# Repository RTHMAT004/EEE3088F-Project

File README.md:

# EEE3088F-Project
Power and Sensing repository for the EEE3088F Project. Group 24: RTHMAT004 and CLRMAT005

This repository contains files for both the sensing and power subsystems of a Micromouse for a university project. This project involved developing a Micromouse, therefore these solutions are built with existing systems in mind (microcontroller, servo motors etc). 

The power system deals with powering the two motors of the Micromouse, managing the charging of the battery and turning the Micromouse on and off.

The sensing system deals with surface detection around the Micromouse, inevitabely helping the micromouse navigate. The sensor does not make decisions of movement, or deal with any power control, it's only purpose is to detect objects and returning results using a voltage output signal. 

# Sensing subsystem:
The folder named "SensorKiCad-RTHMAT004" contains the KiCad files for the sensor subsystem. This subsystem solves the problem of sensing for the micromouse. This subsystem uses IR frequencies to detect objects within the bounds of the sensor. This subsystem solution should be used as a springboard for ideas surrounding sensing for devices such as a micromouse.  

# Power Subsytem
The folder named "PowerKiCad-CLRMAT005" contains the KiCad files for the power subsystem. This subsystem manages everything involving the powering of the Micromouse. This subsystem uses integrated circuits to control the motors and charging of the mouse. This subsystem solution should be used as a springboard for ideas surrounding the powering of small robotics.

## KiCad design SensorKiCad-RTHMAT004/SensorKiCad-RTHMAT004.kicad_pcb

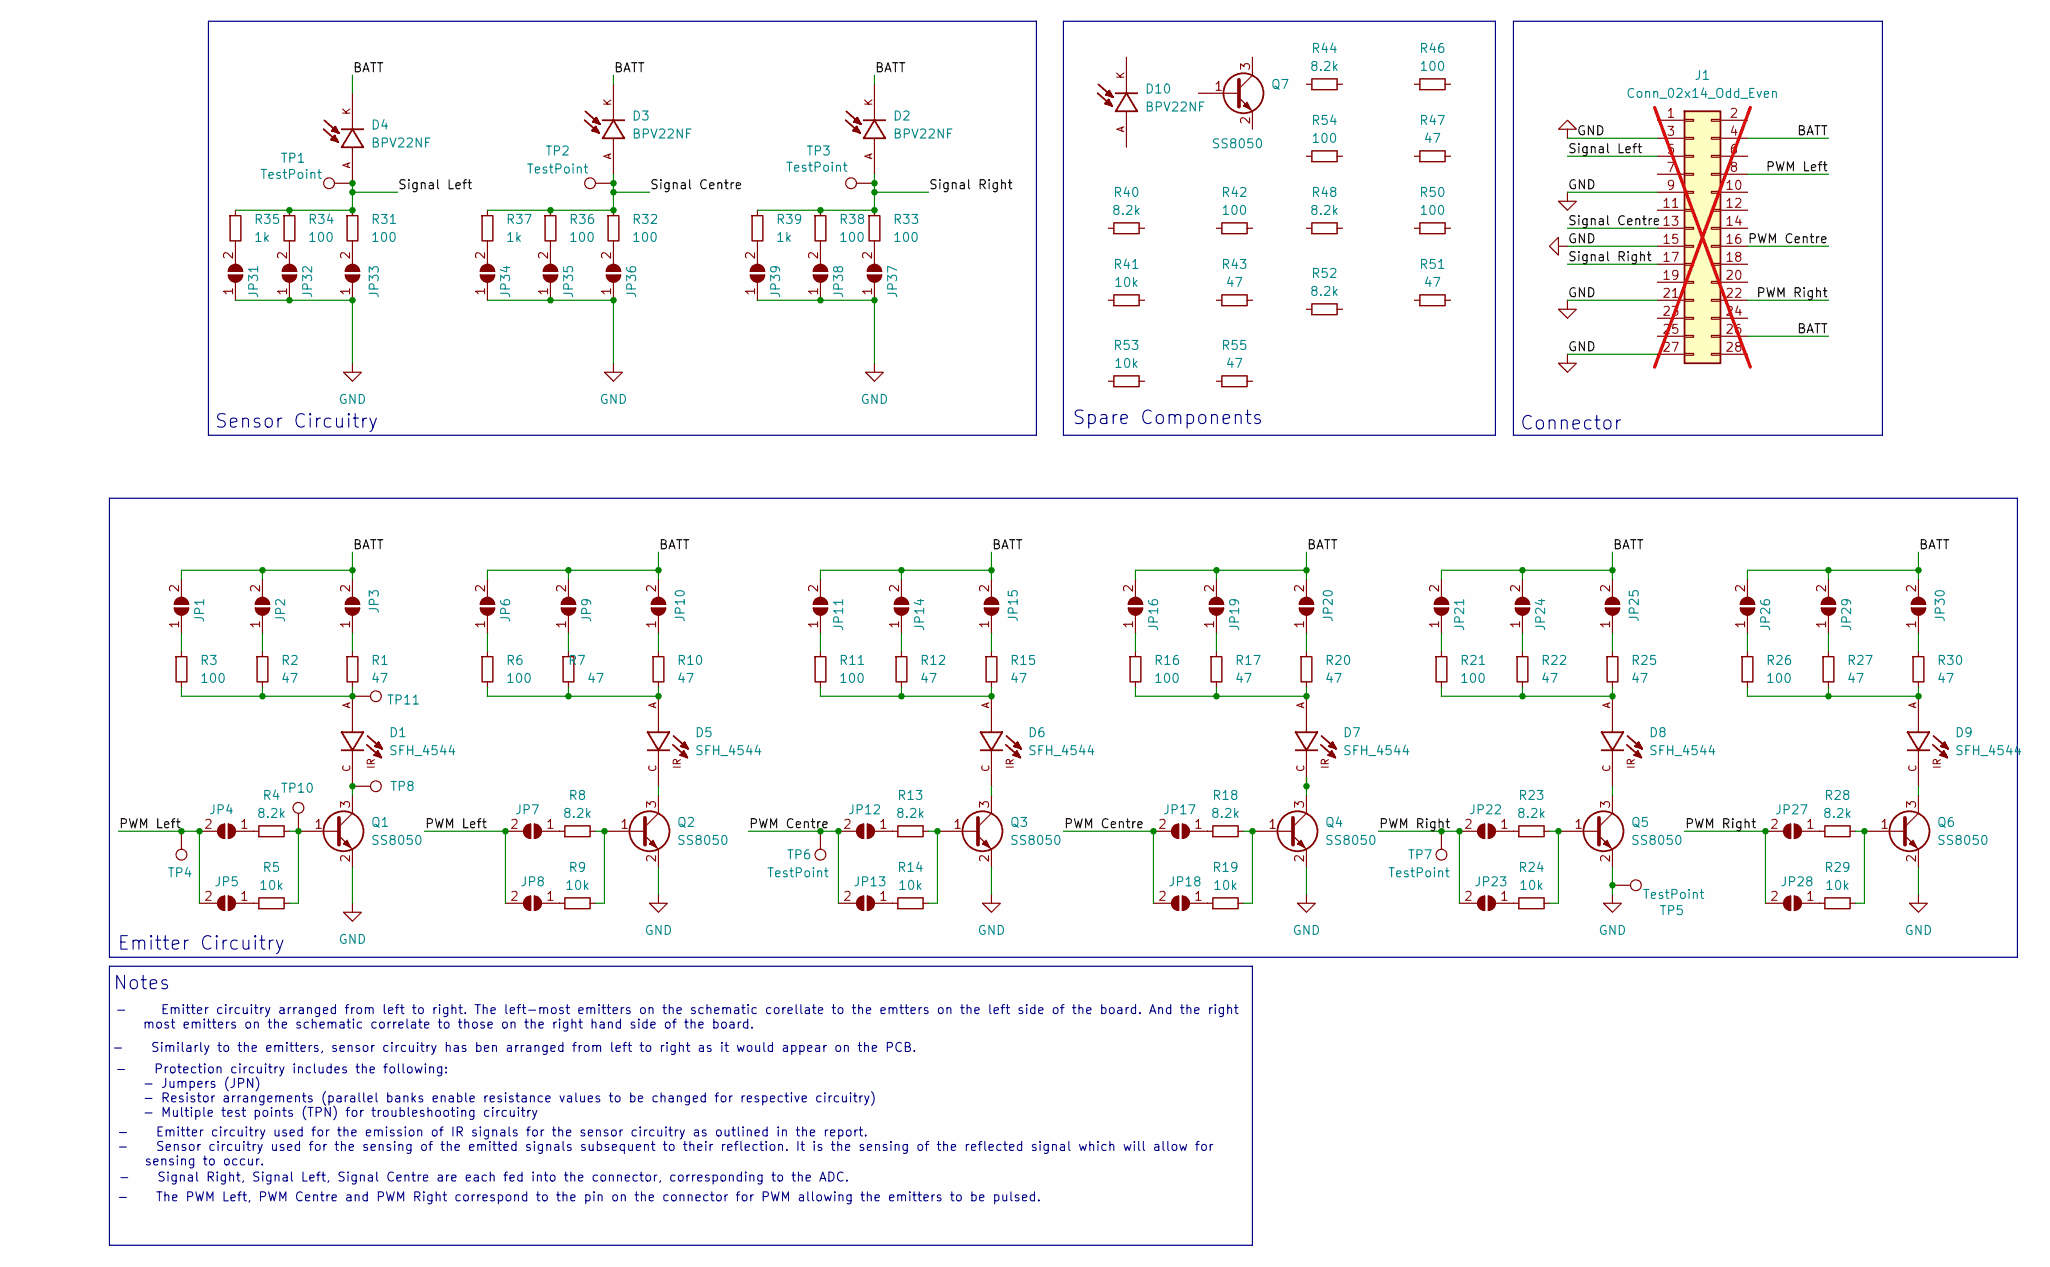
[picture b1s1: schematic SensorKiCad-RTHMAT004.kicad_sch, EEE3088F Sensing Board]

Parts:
D1, D5, D6, D7, D8, D9: SFH_4544; LED_D5.0mm_Horizontal_O1.27mm_Z3.0mm_IRBlack_JLCPCB; PARTREV 1.3; LCSC C2900370
D2, D3, D4, D10: BPV22NF; XDCR_BPV22NF; PARTREV 1.9; LCSC C130226
J1: Conn_02x14_Odd_Even; PinHeader_2x14_P2.54mm_Vertical; not fitted
JP1, JP2, JP3, JP4, JP5, JP6, JP7, JP8, JP9, JP10, JP11, JP12, JP13, JP14, JP15, JP16, JP17, JP18, JP19, JP20, JP21, JP22, JP23, JP24, JP25, JP26, JP27, JP28, JP29, JP30, JP31, JP32, JP33, JP34, JP35, JP36, JP37, JP38, JP39: SolderJumper_2_Open; SolderJumper-2_P1.3mm_Open_Pad1.0x1.5mm
Q1, Q2, Q3, Q4, Q5, Q6, Q7: SS8050; SOT-23; LCSC C2150
R1, R2, R7, R10, R12, R15, R17, R20, R22, R25, R27, R30, R43, R47, R51, R55: 47; R_0805_2012Metric; LCSC C17714
R3, R6, R11, R16, R21, R26, R31, R32, R33, R34, R36, R38, R42, R46, R50, R54: 100; R_0805_2012Metric; LCSC C17901
R4, R8, R13, R18, R23, R28, R40, R44, R48, R52: 8.2k; R_0805_2012Metric; LCSC C17828
R5, R9, R14, R19, R24, R29, R41, R53: 10k; R_1206_3216Metric; LCSC C17902
R35, R37, R39: 1k; R_1206_3216Metric; LCSC C4410
TP1, TP2, TP3, TP4, TP5, TP6, TP7, TP8, TP10, TP11: TestPoint; TestPoint_Pad_D2.5mm

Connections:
/3V3: J1.2
/BATT: D2.K, D3.K, D4.K, J1.4, J1.26, JP1.2 (B), JP2.2 (B), JP3.2 (B), JP6.2 (B), JP9.2 (B), JP10.2 (B), JP11.2 (B), JP14.2 (B), JP15.2 (B), JP16.2 (B), JP19.2 (B), JP20.2 (B), JP21.2 (B), JP24.2 (B), JP25.2 (B), JP26.2 (B), JP29.2 (B), JP30.2 (B)
/PWM Centre: J1.16, JP12.2 (B), JP13.2 (B), JP17.2 (B), JP18.2 (B), TP6.1
/PWM Left: J1.8, JP4.2 (B), JP5.2 (B), JP7.2 (B), JP8.2 (B), TP4.1
/PWM Right: J1.22, JP22.2 (B), JP23.2 (B), JP27.2 (B), JP28.2 (B), TP7.1
/Signal Centre: D3.A, J1.13, R32.1, R36.1, R37.1, TP2.1
/Signal Left: D4.A, J1.5, R31.1, R34.1, R35.1, TP1.1
/Signal Right: D2.A, J1.17, R33.1, R38.1, R39.1, TP3.1
GND: J1.3, J1.9, J1.15, J1.21, J1.27, JP31.1 (A), JP32.1 (A), JP33.1 (A), JP34.1 (A), JP35.1 (A), JP36.1 (A), JP37.1 (A), JP38.1 (A), JP39.1 (A), Q1.2 (E), Q2.2 (E), Q3.2 (E), Q4.2 (E), Q5.2 (E), Q6.2 (E), TP5.1
unnamed: D1.A, R1.2, R2.2, R3.2, TP11.1
unnamed: D5.A, R6.2, R7.2, R10.2
unnamed: D6.A, R11.2, R12.2, R15.2
unnamed: D7.A, R16.2, R17.2, R20.2
unnamed: D8.A, R21.2, R22.2, R25.2
unnamed: D9.A, R26.2, R27.2, R30.2
unnamed: JP1.1 (A), R3.1
unnamed: JP2.1 (A), R2.1
unnamed: JP3.1 (A), R1.1
unnamed: JP4.1 (A), R4.1
unnamed: JP5.1 (A), R5.1
unnamed: JP6.1 (A), R6.1
unnamed: JP7.1 (A), R8.1
unnamed: JP8.1 (A), R9.1
unnamed: JP9.1 (A), R7.1
unnamed: JP10.1 (A), R10.1
unnamed: JP11.1 (A), R11.1
unnamed: JP12.1 (A), R13.1
unnamed: JP13.1 (A), R14.1
unnamed: JP14.1 (A), R12.1
unnamed: JP15.1 (A), R15.1
unnamed: JP16.1 (A), R16.1
unnamed: JP17.1 (A), R18.1
unnamed: JP18.1 (A), R19.1
unnamed: JP19.1 (A), R17.1
unnamed: JP20.1 (A), R20.1
unnamed: JP21.1 (A), R21.1
unnamed: JP22.1 (A), R23.1
unnamed: JP23.1 (A), R24.1
unnamed: JP24.1 (A), R22.1
unnamed: JP25.1 (A), R25.1
unnamed: JP26.1 (A), R26.1
unnamed: JP27.1 (A), R28.1
unnamed: JP28.1 (A), R29.1
unnamed: JP29.1 (A), R27.1
unnamed: JP30.1 (A), R30.1
unnamed: JP31.2 (B), R35.2
unnamed: JP32.2 (B), R34.2
unnamed: JP33.2 (B), R31.2
unnamed: JP34.2 (B), R37.2
unnamed: JP35.2 (B), R36.2
unnamed: JP36.2 (B), R32.2
unnamed: JP37.2 (B), R33.2
unnamed: JP38.2 (B), R38.2
unnamed: JP39.2 (B), R39.2
unnamed: Q1.1 (B), R4.2, R5.2, TP10.1
unnamed: D1.C, Q1.3 (C), TP8.1
unnamed: Q2.1 (B), R8.2, R9.2
unnamed: D5.C, Q2.3 (C)
unnamed: Q3.1 (B), R13.2, R14.2
unnamed: D6.C, Q3.3 (C)
unnamed: Q4.1 (B), R18.2, R19.2
unnamed: D7.C, Q4.3 (C)
unnamed: Q5.1 (B), R23.2, R24.2
unnamed: D8.C, Q5.3 (C)
unnamed: Q6.1 (B), R28.2, R29.2
unnamed: D9.C, Q6.3 (C)

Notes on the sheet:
- Protection circuitry includes the following: - Jumpers (JPN) - Resistor arrangements (parallel banks enable resistance values to be changed for respective circuitry) - Multiple test points (TPN) for troubleshooting circuitry
Spare Components
Notes
- Emitter circuitry arranged from left to right. The left-most emitters on the schematic corellate to the emtters on the left side of the board. And the right most emitters on the schematic correlate to those on the right hand side of the board.
Emitter Circuitry
- Emitter circuitry used for the emission of IR signals for the sensor circuitry as outlined in the report. - Sensor circuitry used for the sensing of the emitted signals subsequent to their reflection. It is the sensing of the reflected signal which will allow for sensing to occur.
Sensor Circuitry
- The PWM Left, PWM Centre and PWM Right correspond to the pin on the connector for PWM allowing the emitters to be pulsed.
- Similarly to the emitters, sensor circuitry has ben arranged from left to right as it would appear on the PCB.
Connector
- Signal Right, Signal Left, Signal Centre are each fed into the connector, corresponding to the ADC.

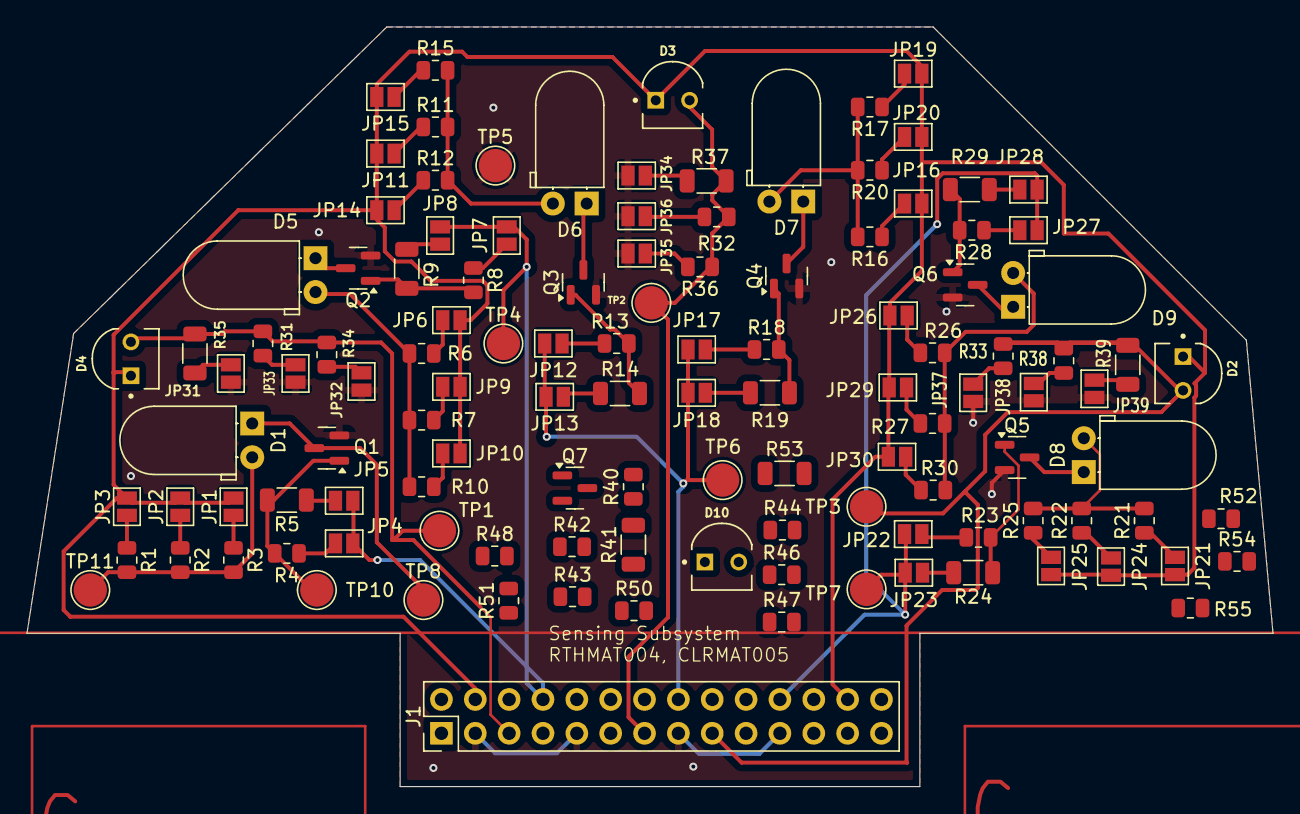
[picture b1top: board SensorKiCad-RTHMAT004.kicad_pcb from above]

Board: 2 copper layers, 93.5 x 57.0 mm, 120 parts (0 on the bottom side), 65 nets.

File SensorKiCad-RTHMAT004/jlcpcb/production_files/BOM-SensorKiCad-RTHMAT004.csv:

Comment,Designator,Footprint,LCSC
BPV22NF,"D10,D2,D3,D4",XDCR_BPV22NF,C130226
47,"R1,R10,R12,R15,R17,R2,R20,R22,R25,R27,R30,R43,R47,R51,R55,R7",R_0805_2012Metric,C17714
8.2k,"R13,R18,R23,R28,R4,R40,R44,R48,R52,R8",R_0805_2012Metric,C17828
100,"R11,R16,R21,R26,R3,R31,R32,R33,R34,R36,R38,R42,R46,R50,R54,R6",R_0805_2012Metric,C17901
10k,"R14,R19,R24,R29,R41,R5,R53,R9",R_1206_3216Metric,C17902
SS8050,"Q1,Q2,Q3,Q4,Q5,Q6,Q7",SOT-23,C2150
SFH_4544,"D1,D5,D6,D7,D8,D9",LED_D5.0mm_Horizontal_O1.27mm_Z3.0mm_IRBlack_JLCPCB,C2900370
1k,"R35,R37,R39",R_1206_3216Metric,C4410

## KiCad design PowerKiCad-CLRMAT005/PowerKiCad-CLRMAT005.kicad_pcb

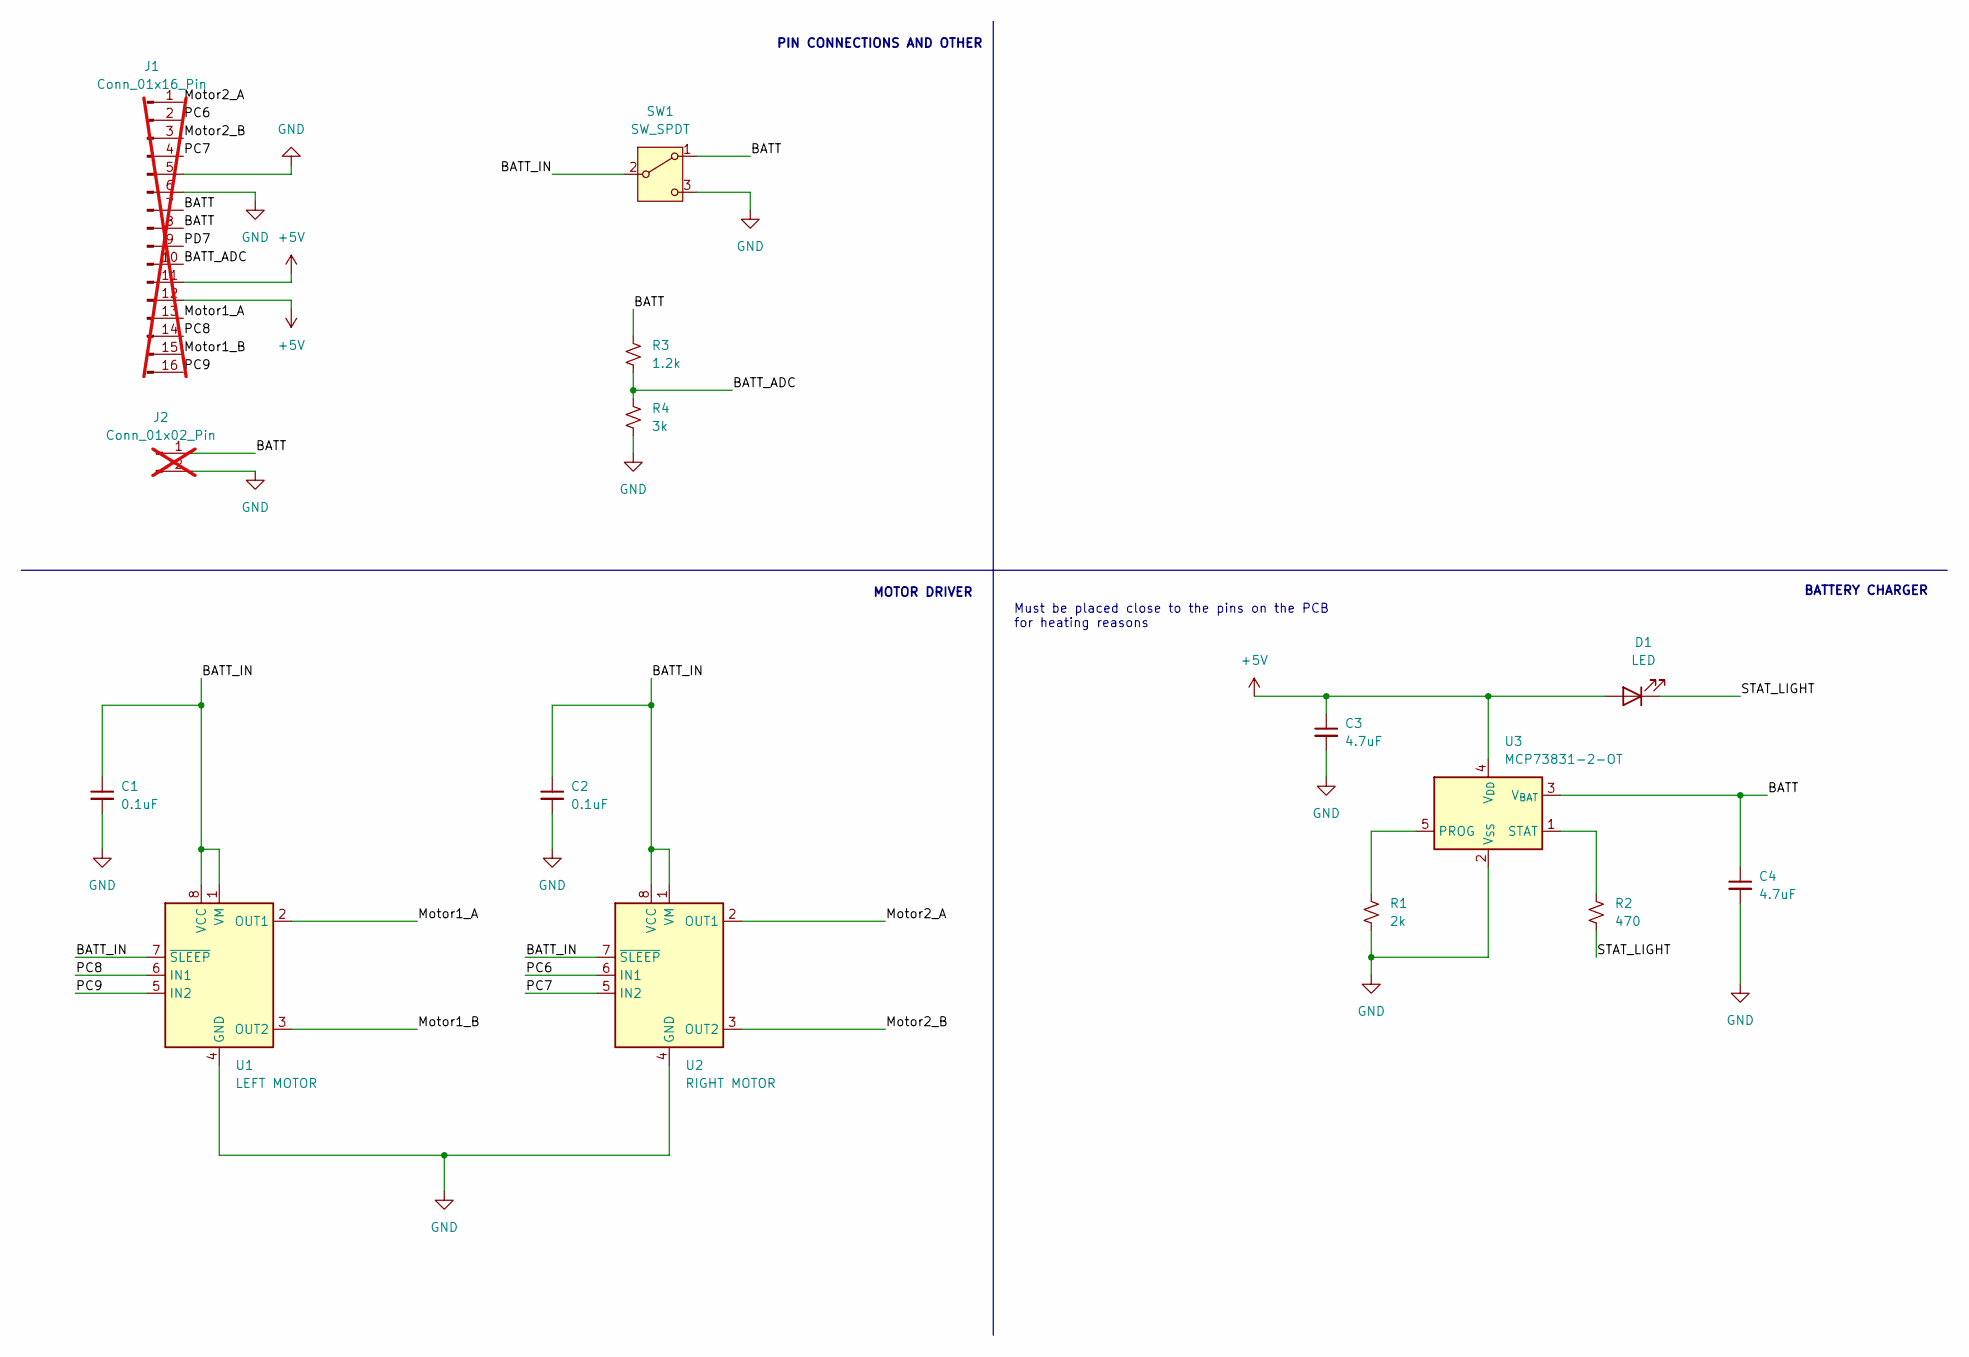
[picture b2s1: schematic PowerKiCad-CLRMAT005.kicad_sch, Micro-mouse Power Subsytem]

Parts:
C1, C2: 0.1uF; C_0603_1608Metric
C3, C4: 4.7uF; C_0805_2012Metric
D1: LED; LED_0603_1608Metric
J1: Conn_01x16_Pin; PinSocket_2x08_P2.54mm_Vertical; not fitted
J2: Conn_01x02_Pin; JST_PH_B2B-PH-K_1x02_P2.00mm_Vertical; not fitted
R1: 2k; R_0402_1005Metric
R2: 470; R_0805_2012Metric
R3: 1.2k; R_0805_2012Metric
R4: 3k; R_0603_1608Metric
SW1: SW_SPDT; SW_Lever_1P2T_NKK_GW12LxH
U1: LEFT MOTOR; WSON-8-1EP_2x2mm_P0.5mm_EP0.9x1.6mm
U2: RIGHT MOTOR; WSON-8-1EP_2x2mm_P0.5mm_EP0.9x1.6mm
U3: MCP73831-2-OT; SOT-23-5

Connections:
+5V: C3.1, D1.2 (A), J1.11, J1.12, U3.4 (V_{DD})
/BATT: C4.1, J1.7, J1.8, J2.1, R3.1, SW1.1 (A), U3.3 (V_{BAT})
/BATT_ADC: J1.10, R3.2, R4.1
/BATT_IN: C1.1, C2.1, SW1.2 (B), U1.1 (VM), U1.7 (~SLEEP), U1.8 (VCC), U2.1 (VM), U2.7 (~SLEEP), U2.8 (VCC)
/Motor1_A: J1.13, U1.2 (OUT1)
/Motor1_B: J1.15, U1.3 (OUT2)
/Motor2_A: J1.1, U2.2 (OUT1)
/Motor2_B: J1.3, U2.3 (OUT2)
/PC6: J1.2, U2.6 (IN1)
/PC7: J1.4, U2.5 (IN2)
/PC8: J1.14, U1.6 (IN1)
/PC9: J1.16, U1.5 (IN2)
/PD7: J1.9
/STAT_LIGHT: D1.1 (K), R2.2
GND: C1.2, C2.2, C3.2, C4.2, J1.5, J1.6, J2.2, R1.2, R4.2, SW1.3 (C), U1.4 (GND), U1.9 (GND), U2.4 (GND), U2.9 (GND), U3.2 (V_{SS})
unnamed: R1.1, U3.5 (PROG)
unnamed: R2.1, U3.1 (STAT)

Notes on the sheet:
PIN CONNECTIONS AND OTHER
BATTERY CHARGER
for heating reasons
Must be placed close to the pins on the PCB
MOTOR DRIVER

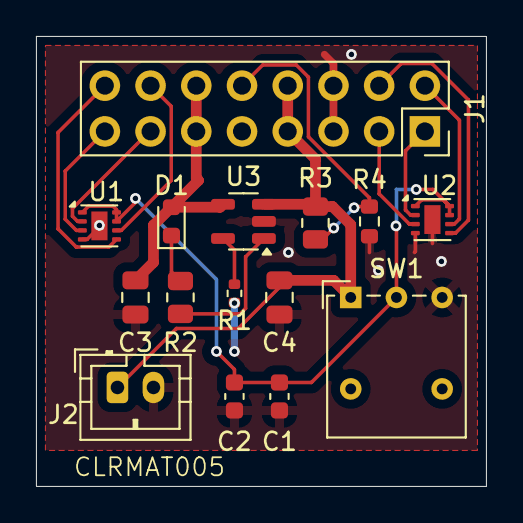
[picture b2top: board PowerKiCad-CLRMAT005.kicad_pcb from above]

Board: 2 copper layers, 25.0 x 25.0 mm, 15 parts (0 on the bottom side), 16 nets.

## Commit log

2024-03-16 Sensor KiCad
2024-03-16 This is my Power KiCad Project
2024-03-16 Unpopulated pins
2024-03-17 Small changes to Sensor KiCAD file
2024-03-21 Finalising PCB
2024-03-21 pcb advancements
2024-03-23 Final changes to sensor
2024-04-10 Finalised KiCad files =
2024-04-10 Removing .zip files
2024-04-16 Final changes to git repo
2024-04-16 added stuff to power subfolder
